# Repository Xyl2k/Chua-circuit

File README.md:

Chua-circuit
============

Simple electronic circuit that exhibits classic chaos theory behavior.
schematic and board layout based on http://powerdown.free.fr/io/a/ach.html

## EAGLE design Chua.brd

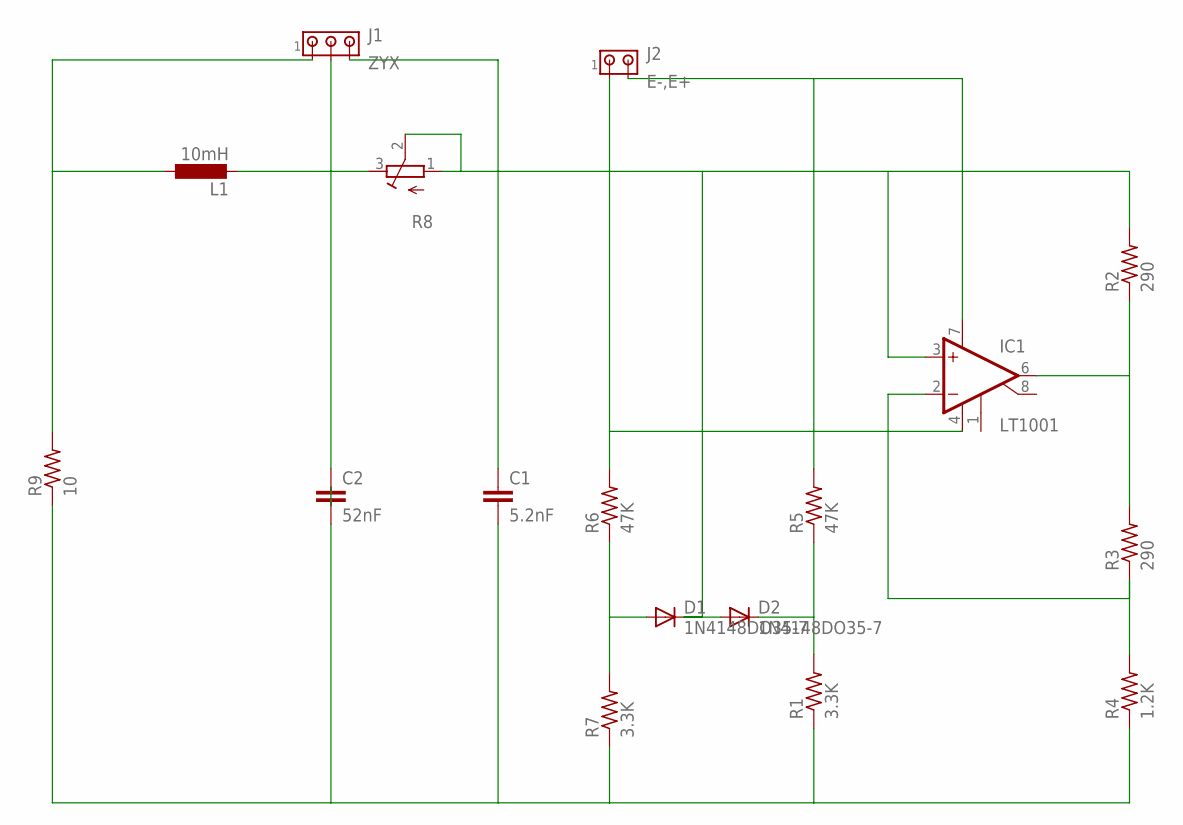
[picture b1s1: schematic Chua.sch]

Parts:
C1: 5.2nF; C025-060X050
C2: 52nF; C025-060X050
D1, D2: 1N4148DO35-7; DO35-7
IC1: LT1001; DIL08
J1: ZYX; 10X03MTA
J2: E-,E+; 10X02MTA
L1: 10mH; 0207/5V
R1, R7: 3.3K; 0204/7
R2, R3: 290; 0204/7
R4: 1.2K; 0204/7
R5, R6: 47K; 0204/7
R8: R-TRIMM3296Y; RTRIM3296Y
R9: 10; 0204/7

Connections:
unnamed: IC1.6 (OUT), R2.1, R3.2
unnamed: C1.2, C2.2, R1.1, R4.1, R7.1, R9.1
unnamed: IC1.2 (-IN), R3.1, R4.2
unnamed: D2.C, R1.2, R5.1
unnamed: D1.A, R6.1, R7.2
unnamed: C1.1, D1.C, D2.A, IC1.3 (+IN), J1.3, R2.2, R8.1 (E), R8.2 (S)
unnamed: C2.1, J1.2, L1.2, R8.3 (A)
unnamed: J1.1, L1.1, R9.2
unnamed: IC1.4 (V-), J2.1, R6.2
unnamed: IC1.7 (V+), J2.2, R5.2

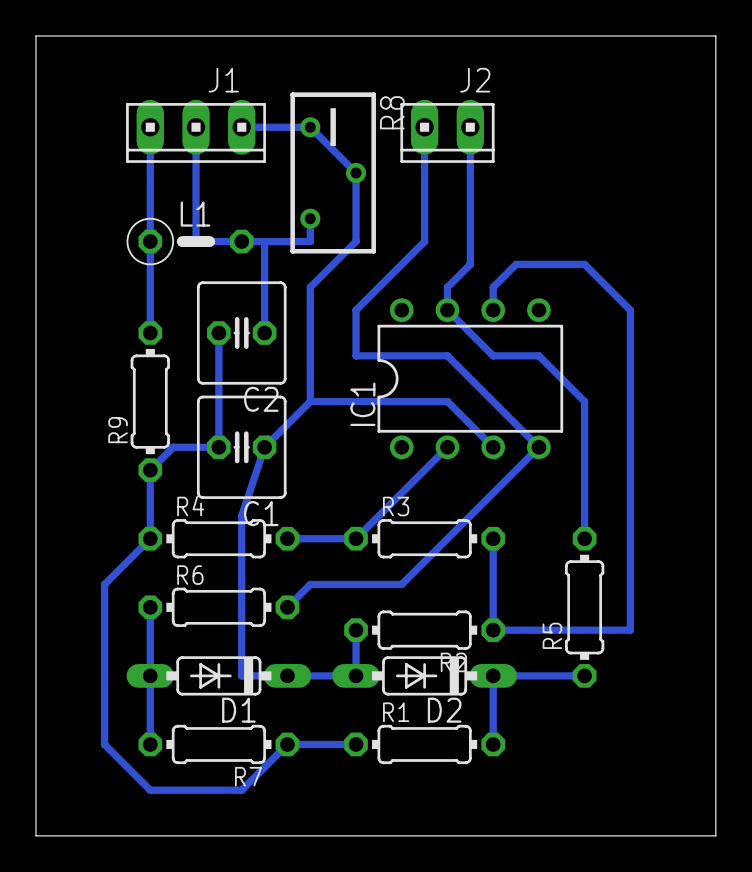
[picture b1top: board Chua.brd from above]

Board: 2 copper layers, 37.8 x 44.4 mm, 17 parts (0 on the bottom side), 10 nets.

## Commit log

2014-12-23 :space_invader: Added .gitattributes & .gitignore files
2014-12-23 1.0
    1.0
2014-12-24 1.1
    Fixed mistake R8 should be a trimmer instead of a resistor.
